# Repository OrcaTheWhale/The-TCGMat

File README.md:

# The-TCGMat
A mat that is designed for TCG! Well, mostly just One Piece TCG and Riftbound.

Notice:
Under "StepFiles", and in the Onshape document, certain parts have "O" at the end of their names. This means that part is optional. If  you would like to save on filament, then you can skip printing the optional parts.

I also assume you have jumper wires. If you don't, what are you doing.

**What is this?**

The TCGMat is a 3D - printable (and thick) mat that integrates LEDS and a screen into your TCG experience! With LED settings, you can turn change the color of your border, alongside the Leader/Legend card border. You can also pass your turn, turning the border leds to red!

The TCGMat has a few built in settings for basic level play, such as Riftbound settings, One Piece settings, and LED settings. 

It also contains **NO** screws, meaning it's literally attach-and-play.

**Why would I use this?**

Great question! Why would you? It IS 2kg of filament... But think about it! Just like the Zine page says, you can absolutely mog your opponent! Think about it. It's a tournament. Or a local game tournament. Your opponent takes out his cool art mat of DaVinci Starry Night Pikachu. And then, you whip out - this thick, 2kg piece of rectangle. Will people think you look stupid? Mmm, maybe. But then, they'll see the LED colors shine at the borders. They'll still think it's stupid, of course, but now, it looks _cool_ stupid. The amount of aura you'll have with the mat will provide a sense of dominance.

**How does this work?**

You take the parts and attach them, no screws needed. You link them using four or two link rectangles given in the CAD/StepFiles. 
For the code, well... It's built based off of pure hopes and dreams. It is about 800 lines of absolutely disgustingly unoptimized code. 
There are three buttons: On/Off, Config, and Action. On/Off is self explanatory. Config is for the settings, it allows scrolling through different options. Action selects those options.

**Why did I make this?**

Great question, reader! I made this to try communication between microcontrollers. Originally, the idea was to have two mats being able to connect to each other and share info, but I gave up on that idea after realising I would have to change... some things... But, the option is still there, if you want to try to go for it yourself.

The reference Transf- (it cut off) is for magnetic pogo pin connectors. You can check the schematic, but RX is labeled for you, if you are going for TX/RX communicaton. A resistor is also already placed on the TX line. If you want to try for communication, go for it!

But I also made this cause my friends play One Piece / Riftbound TCG. I, myself only play Riftbound, but I thought it'd be cooler to have more than one game option on the TCG Mat. I also have no idea how to play other TCG's, so that's why the only options are Riftbound and One Piece.

**For the TCG fans:**

Take a shower.

Zine Page!

PCB:

Schematic:

CAD Model:

CAD: https://cad.onshape.com/documents/c90b06010f75d3568477ea12/w/fd36c3df957e31bf29fadb32/e/bceb6737e14c83207b7cbead?renderMode=0&uiState=6a0e5ef42757ca4fdc8010bd

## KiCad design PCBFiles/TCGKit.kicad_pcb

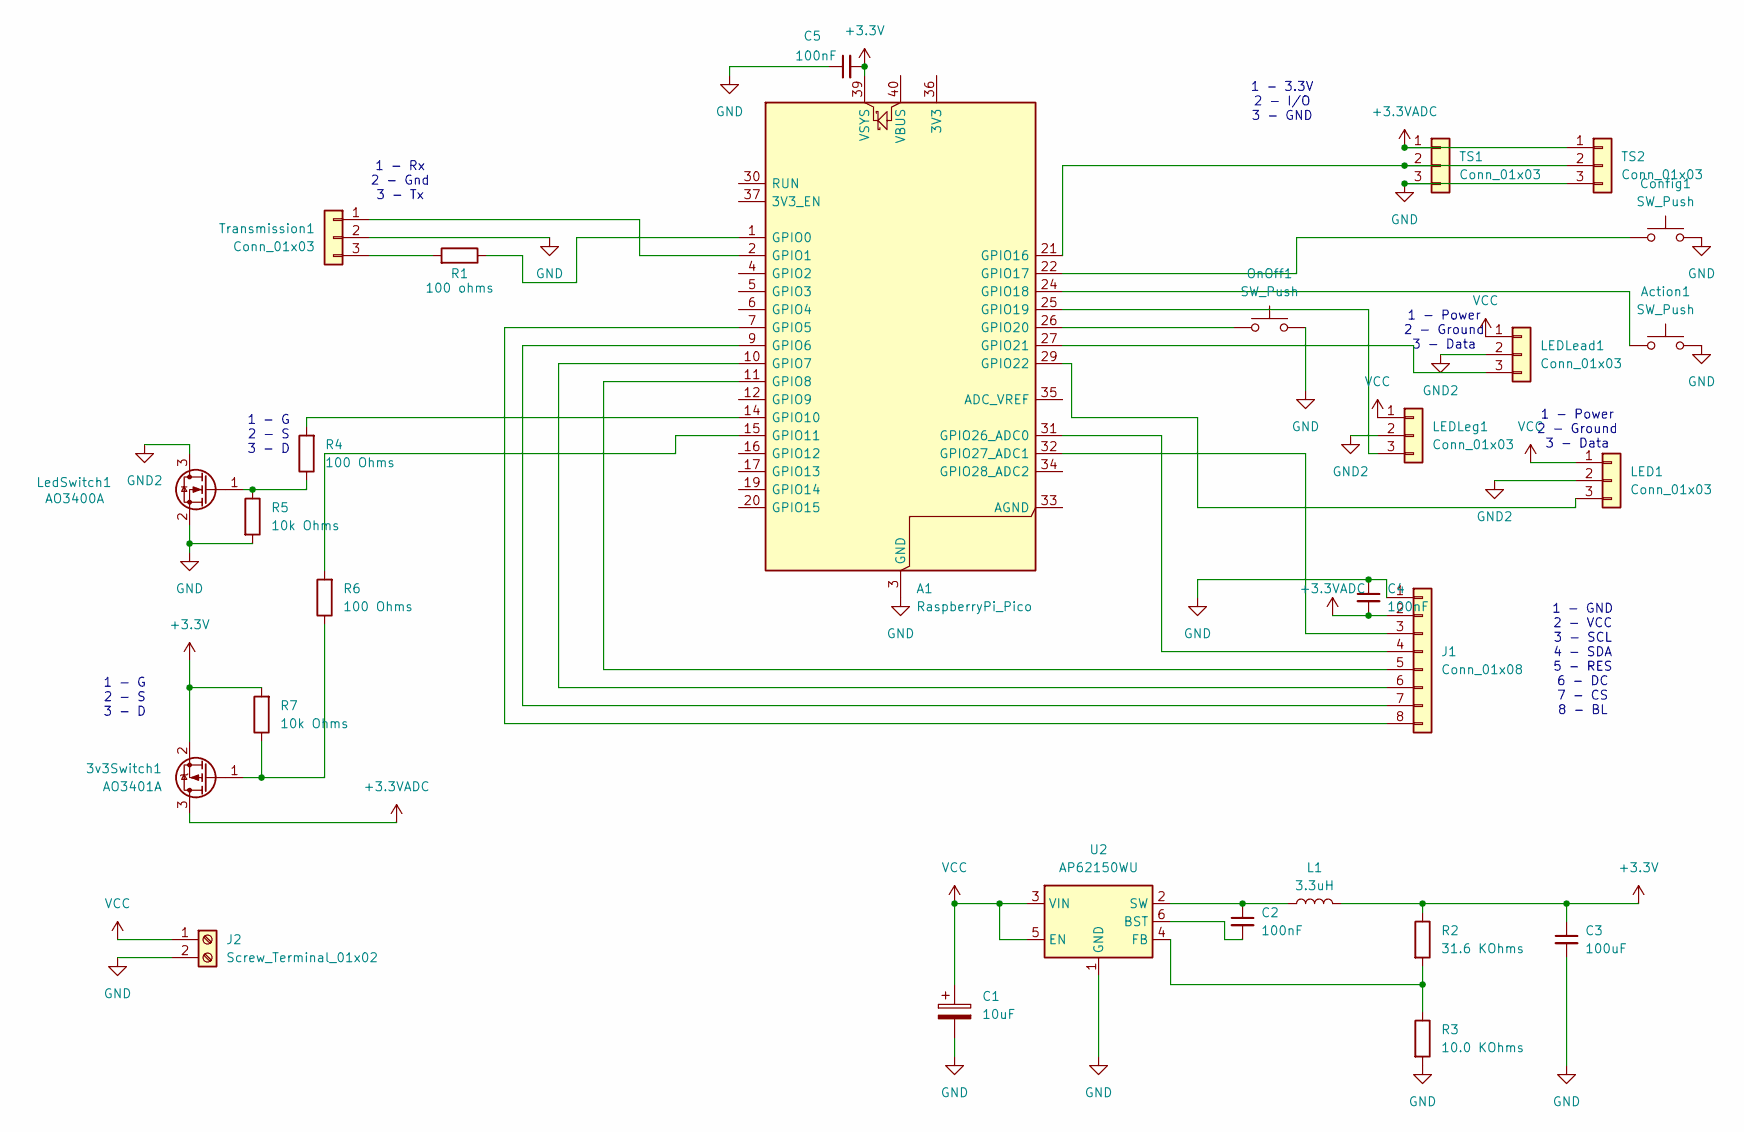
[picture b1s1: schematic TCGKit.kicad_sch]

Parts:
3v3Switch1: AO3401A; SOT-23
A1: RaspberryPi_Pico; RaspberryPi_Pico_Common_Unspecified
Action1: SW_Push; SW_PUSH_6mm
C1: 10uF; CP_Radial_D5.0mm_P2.00mm
C2, C4, C5: 100nF; C_0805_2012Metric_Pad1.18x1.45mm_HandSolder
C3: 100uF; CP_Radial_D5.0mm_P2.00mm
Config1: SW_Push; SW_PUSH_6mm
J1: Conn_01x08; PinSocket_1x08_P2.54mm_Vertical
J2: Screw_Terminal_01x02; TerminalBlock_Phoenix_MPT-0,5-2-2.54_1x02_P2.54mm_Horizontal
L1: 3.3uH; IND_TAIYO_NRS4018_TAY
LED1: Conn_01x03; PinHeader_1x03_P2.54mm_Vertical
LEDLead1: Conn_01x03; PinHeader_1x03_P2.54mm_Vertical
LEDLeg1: Conn_01x03; PinHeader_1x03_P2.54mm_Vertical
LedSwitch1: AO3400A; SOT-23
OnOff1: SW_Push; SW_PUSH_6mm
R1: 100 ohms; R_Axial_DIN0207_L6.3mm_D2.5mm_P10.16mm_Horizontal
R2: 31.6 KOhms; R_0402_1005Metric_Pad0.72x0.64mm_HandSolder
R3: 10.0 KOhms; R_Axial_DIN0207_L6.3mm_D2.5mm_P10.16mm_Horizontal
R4, R6: 100 Ohms; R_Axial_DIN0207_L6.3mm_D2.5mm_P10.16mm_Horizontal
R5, R7: 10k Ohms; R_Axial_DIN0207_L6.3mm_D2.5mm_P10.16mm_Horizontal
TS1, TS2: Conn_01x03; PinHeader_1x03_P2.54mm_Vertical
Transmission1: Conn_01x03; PinHeader_1x03_P2.54mm_Horizontal
U2: AP62150WU; TSOT-23-6

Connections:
+3.3V: 3v3Switch1.2 (S), A1.39 (VSYS), C3.1, C5.2, L1.2, R2.1, R7.2
+3.3VADC: 3v3Switch1.3 (D), C4.2, J1.2, TS1.1, TS2.1
GND: A1.3 (GND), A1.8 (GND), A1.13 (GND), A1.18 (GND), A1.23 (GND), A1.28 (GND), A1.38 (GND), Action1.2, C1.2, C3.2, C4.1, C5.1, Config1.2, J1.1, J2.2, LedSwitch1.2 (S), OnOff1.2, R3.2, R5.2, TS1.3, TS2.3, Transmission1.2, U2.1 (GND)
GND2: LED1.2, LEDLead1.2, LEDLeg1.2, LedSwitch1.3 (D)
unnamed: 3v3Switch1.1 (G), R6.1, R7.1
unnamed: A1.1 (GPIO0), R1.1
unnamed: A1.2 (GPIO1), Transmission1.1
unnamed: A1.7 (GPIO5), J1.8
unnamed: A1.9 (GPIO6), J1.7
unnamed: A1.10 (GPIO7), J1.6
unnamed: A1.11 (GPIO8), J1.5
unnamed: A1.14 (GPIO10), R4.2
unnamed: A1.15 (GPIO11), R6.2
unnamed: A1.21 (GPIO16), TS1.2, TS2.2
unnamed: A1.22 (GPIO17), Config1.1
unnamed: A1.24 (GPIO18), Action1.1
unnamed: A1.25 (GPIO19), LEDLeg1.3
unnamed: A1.26 (GPIO20), OnOff1.1
unnamed: A1.27 (GPIO21), LEDLead1.3
unnamed: A1.29 (GPIO22), LED1.3
unnamed: A1.31 (GPIO26_ADC0), J1.4
unnamed: A1.32 (GPIO27_ADC1), J1.3
unnamed: LedSwitch1.1 (G), R4.1, R5.1
unnamed: R1.2, Transmission1.3
unnamed: C2.2, U2.6 (BST)
unnamed: R2.2, R3.1, U2.4 (FB)
unnamed: C2.1, L1.1, U2.2 (SW)
VCC: C1.1, J2.1, LED1.1, LEDLead1.1, LEDLeg1.1, U2.3 (VIN), U2.5 (EN)

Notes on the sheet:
1 - Power 2 - Ground 3 - Data
1 - 3.3V 2 - I/O 3 - GND
1 - Rx 2 - Gnd 3 - Tx
1 - GND 2 - VCC 3 - SCL 4 - SDA 5 - RES 6 - DC 7 - CS 8 - BL
1 - G 2 - S 3 - D

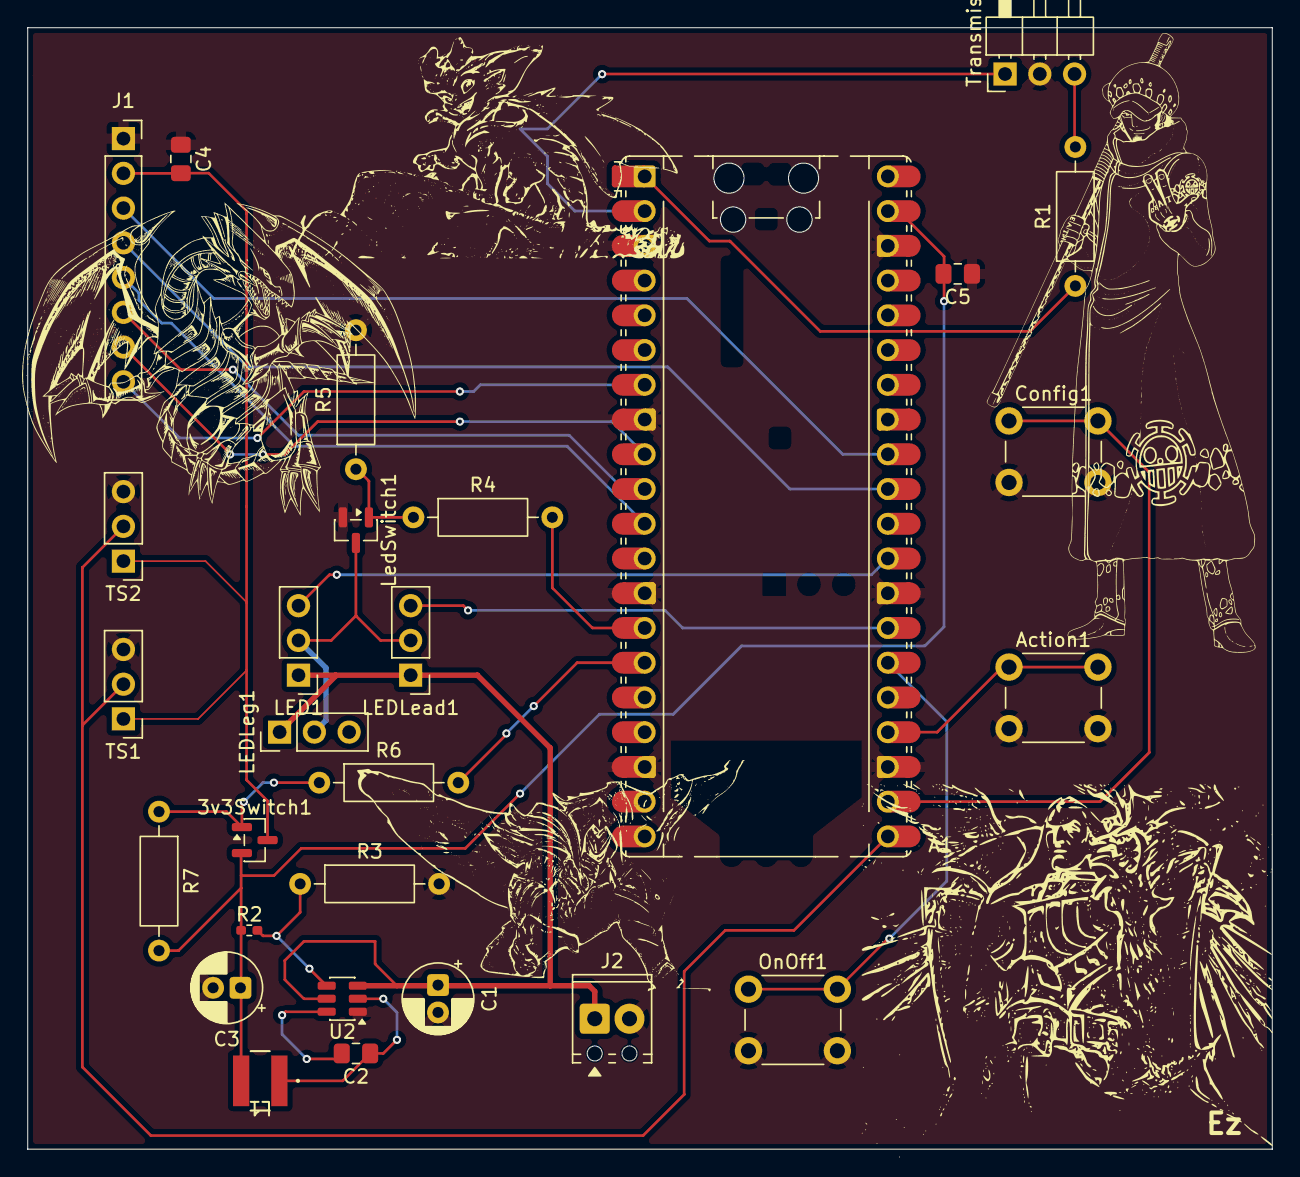
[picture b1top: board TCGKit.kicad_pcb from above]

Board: 4 copper layers, 91.0 x 82.0 mm, 28 parts (0 on the bottom side), 28 nets.

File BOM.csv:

Component,Quantity,Price (CAD),REF,Link
TCGMat PCB (JLCPCB),1,10.97,,
COB LED 2 meters,1,23.40,,https://www.aliexpress.com/item/1005005046710332.html?spm=a2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
TFT Display,1,4.67,J1,https://www.aliexpress.com/item/1005006139989470.html?spm=a2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
Touch Sensors,1-2,3.24,TouchSensor1/TouchSensor2Ghost,https://www.aliexpress.com/item/1005006246380749.html?spm=a2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
31.6k Ohms Resistor,1,0.17,C2,https://www.digikey.ca/en/products/detail/panasonic-industry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
N-Channel Mosfet,1,0.80,LedSwitch1,https://www.digikey.ca/en/products/detail/alpha-omega-semico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
P-Channel Mosfet,1,0.80,3v3Switch1,https://www.digikey.ca/en/products/detail/alpha-omega-semico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
"Charging Module, 12v Boost With Box",1,3.96,,https://www.aliexpress.com/item/1005005631366128.html?spm=a2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
3.3 uH Inductor,1,0.27,L1,https://www.digikey.ca/en/products/detail/taiyo-yuden/NRS401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
Buck IC,1,0.62,U2,https://www.digikey.ca/en/products/detail/diodes-incorporate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
100 Ohms Resistor (Kit),3,,"R1, R4, R6",
10k Ohms Resistor (Kit),1,5.75,"R3, R5, R7",https://www.aliexpress.com/item/1005011772534173.html?spm=a2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
100 nF Capacitor SMD,2,3.55,"C2, C4",https://www.aliexpress.com/item/32964553793.html?spm=a2g0o.p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
10 uF Capacitor TH,1,3.53,C1,https://www.aliexpress.com/item/1005002524973878.html?spm=a2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
100 uF Capacitor TH,1,4.07,C3,https://www.aliexpress.com/item/1005002524973878.html?spm=a2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
Screw Terminal 2.54mm,2,2.38,"J2, Code1",https://www.aliexpress.com/item/4000867583795.html?spm=a2g0o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
Pin Header 2.54mm 01x40 (snap off),1,6.50,(LED1)/(LEDLead/Leg1),https://www.aliexpress.com/item/1005007564228387.html?spm=a2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
Switch Buttons 6x6mm,3,2.29,"OnOff1, Config1, Action1",https://www.aliexpress.com/item/1005006046180384.html?spm=a2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
Raspberry Pi Pico,1,4.59,,https://www.digikey.ca/en/products/detail/raspberry-pi/SC091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
PLA Filament (1kg),2,51.98,,https://ca.store.bambulab.com/products/pla-basic-filament?id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
Digikey Shipping,1,25.00,,
Tax,,17.36,,
Total:,,164.93,,

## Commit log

2026-05-16 Rename TCGMat Bill of Materials - Sheet1.csv to BOM.csv
2026-05-20 Rename TCGMat Bill of Materials - Sheet1 (1).csv to BOM.csv
2026-05-20 Rename TCGMat Bill of Materials - Sheet1 (2).csv to BOM.csv
